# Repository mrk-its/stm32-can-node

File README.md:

# STM32 CAN Node

# Features

* modern STM32 MCU (U3/U5 series)
* integrated step-down converter (24V -> 3.3V)
* integrated CAN transceiver
* integrated 1-wire master controller (over i2c)
* 2.54 pin headers exposing 15 GPIOs
* separate SWD connector for flashing / debugging
* separate UART connector
* small form factor (40mm x 25mm)

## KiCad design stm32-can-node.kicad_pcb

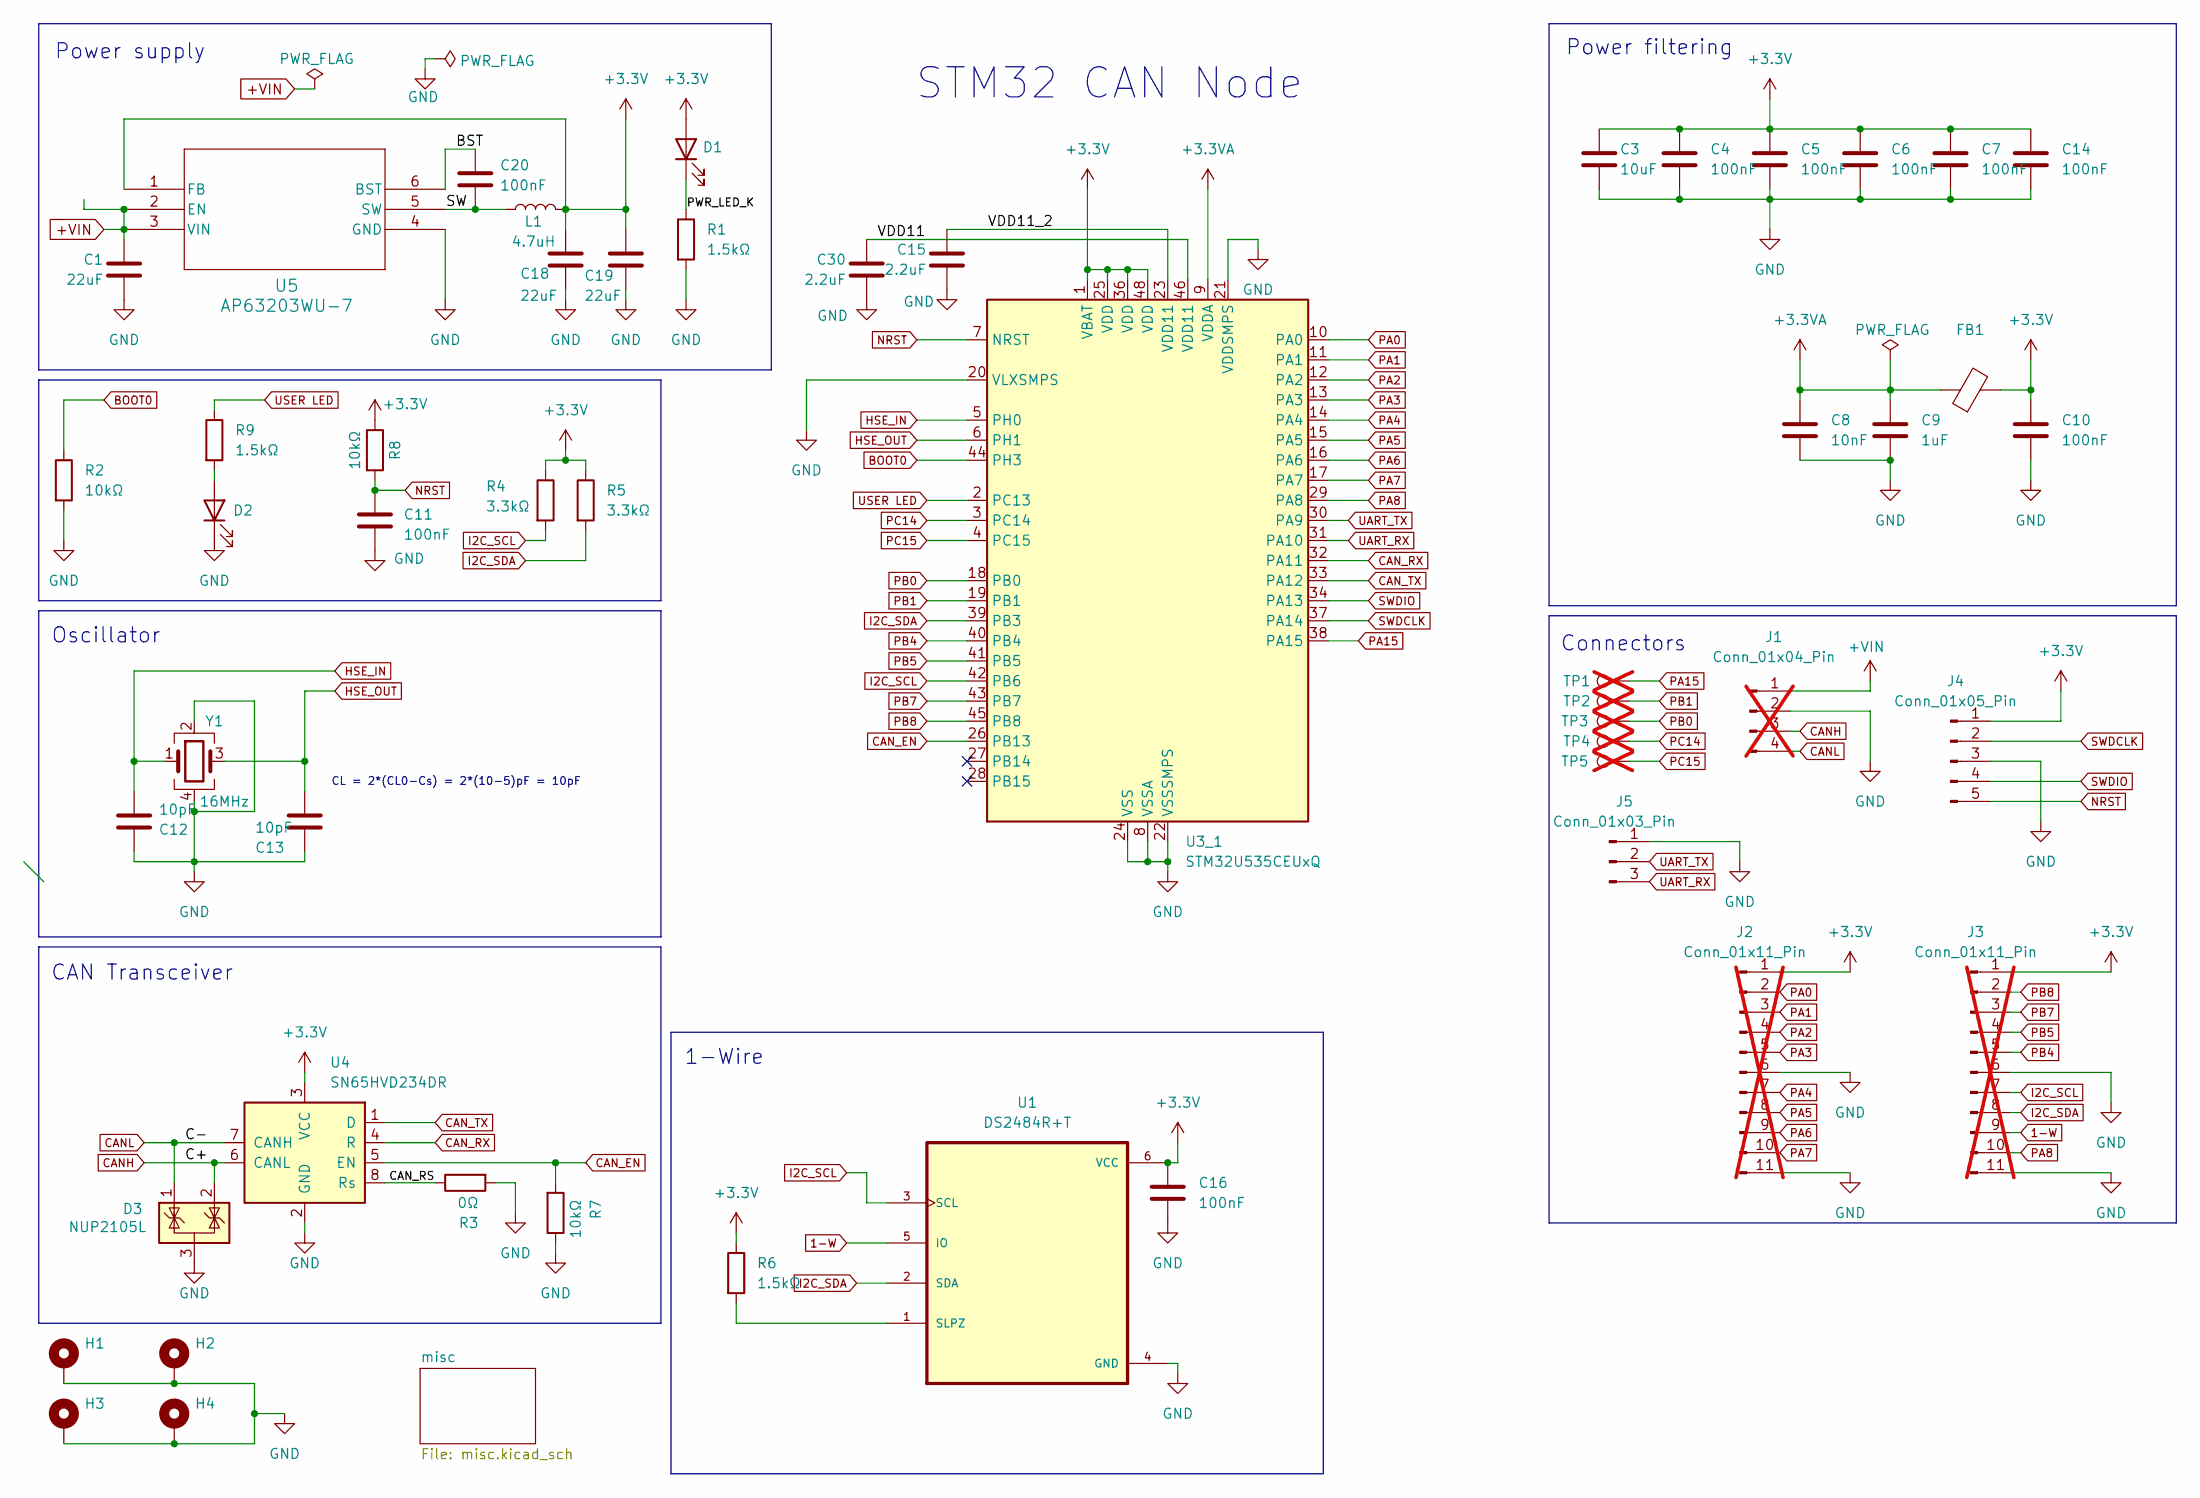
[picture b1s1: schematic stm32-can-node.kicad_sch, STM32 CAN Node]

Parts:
C1: 22uF; C_0805_2012Metric
C3: 10uF; C_0603_1608Metric
C4, C5, C6, C7, C10, C11, C14, C16, C20: 100nF; C_0402_1005Metric
C8: 10nF; C_0402_1005Metric
C9: 1uF; C_0402_1005Metric
C12, C13: 10pF; C_0402_1005Metric
C15, C30: 2.2uF; C_0603_1608Metric
C18, C19: 22uF; C_0603_1608Metric
D1: C397045; LED_0402_1005Metric
D2: C165977; LED_0402_1005Metric
D3: NUP2105L; SOT-23
FB1: FCM1608KF-601T05; L_0603_1608Metric; JLC C133937
H1, H2, H3, H4: MountingHole_Pad; MountingHole_2.2mm_M2_DIN965_Pad
J1: Conn_01x04_Pin; PinHeader_1x04_P2.54mm_Vertical; not fitted
J2, J3: Conn_01x11_Pin; PinHeader_1x11_P2.54mm_Vertical; not fitted
J4: Conn_01x05_Pin; PinHeader_1x05_P1.27mm_Vertical; JLC C2935945
J5: Conn_01x03_Pin; PinHeader_1x03_P1.27mm_Vertical; JLC C2935943
L1: 4.7uH; IND_SRP4020TA-4R7M
R1, R6, R9: 1.5kΩ; R_0402_1005Metric
R2, R7, R8: 10kΩ; R_0402_1005Metric
R3: 0Ω; R_0402_1005Metric
R4, R5: 3.3kΩ; R_0402_1005Metric
TP1, TP2, TP3, TP4, TP5: TestPoint; mini_test_point; not fitted
U1: DS2484R+T; DS2484; JLC C124886
U3_1: STM32U535CEUxQ; QFN-48-1EP_7x7mm_P0.5mm_EP5.6x5.6mm; JLC C22453481
U4: SN65HVD234DR; SOIC-8_3.9x4.9mm_P1.27mm; JLC C99818
U5: AP63203WU-7; AP63203WU-7_DIO; JLC C780769
Y1: 16MHz; Crystal_SMD_3225-4Pin_3.2x2.5mm; JLC C13738

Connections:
1-W: J3.9, U1.5 (IO)
+3.3V: C3.1, C4.1, C5.1, C6.1, C7.1, C10.1, C14.1, C16.1, C18.1, C19.1, D1.2 (A), FB1.2, J2.1, J3.1, J4.1, L1.2, R4.1, R5.1, R6.1, R8.1, U1.6 (VCC), U3_1.1 (VBAT), U3_1.25 (VDD), U3_1.36 (VDD), U3_1.48 (VDD), U4.3 (VCC), U5.1 (FB)
+3.3VA: C8.1, C9.1, FB1.1, U3_1.9 (VDDA)
+VIN: C1.1, J1.1, U5.2 (EN), U5.3 (VIN)
/BST: C20.1, U5.6 (BST)
/CAN_RS: R3.1, U4.8 (Rs)
/PWR_LED_K: D1.1 (K), R1.1
/SW: C20.2, L1.1, U5.5 (SW)
/VDD11: C30.1, U3_1.46 (VDD11)
/VDD11_2: C15.1, U3_1.23 (VDD11)
BOOT0: R2.1, U3_1.44 (PH3)
CANH: D3.2 (K), J1.3, U4.6 (CANL)
CANL: D3.1 (K), J1.4, U4.7 (CANH)
CAN_EN: R7.2, U3_1.26 (PB13), U4.5 (EN)
CAN_RX: U3_1.32 (PA11), U4.4 (R)
CAN_TX: U3_1.33 (PA12), U4.1 (D)
GND: C1.2, C3.2, C4.2, C5.2, C6.2, C7.2, C8.2, C9.2, C10.2, C11.1, C12.2, C13.2, C14.2, C15.2, C16.2, C18.2, C19.2, C30.2, D2.1 (K), D3.3 (A), H1.1, H2.1, H3.1, H4.1, J1.2, J2.6, J2.11, J3.6, J3.11, J4.3, J5.1, R1.2, R2.2, R3.2, R7.1, U1.4 (GND), U3_1.8 (VSSA), U3_1.20 (VLXSMPS), U3_1.21 (VDDSMPS), U3_1.22 (VSSSMPS), U3_1.24 (VSS), U3_1.35 (VSS), U3_1.47 (VSS), U3_1.49 (VSS), U4.2 (GND), U5.4 (GND), Y1.2, Y1.4
HSE_IN: C12.1, U3_1.5 (PH0), Y1.1
HSE_OUT: C13.1, U3_1.6 (PH1), Y1.3
I2C_SCL: J3.7, R4.2, U1.3 (SCL), U3_1.42 (PB6)
I2C_SDA: J3.8, R5.2, U1.2 (SDA), U3_1.39 (PB3)
NRST: C11.2, J4.5, R8.2, U3_1.7 (NRST)
unnamed: D2.2 (A), R9.2
unnamed: R6.2, U1.1 (SLPZ)
PA0: J2.2, U3_1.10 (PA0)
PA1: J2.3, U3_1.11 (PA1)
PA2: J2.4, U3_1.12 (PA2)
PA3: J2.5, U3_1.13 (PA3)
PA4: J2.7, U3_1.14 (PA4)
PA5: J2.8, U3_1.15 (PA5)
PA6: J2.9, U3_1.16 (PA6)
PA7: J2.10, U3_1.17 (PA7)
PA8: J3.10, U3_1.29 (PA8)
PA15: TP1.1, U3_1.38 (PA15)
PB0: TP3.1, U3_1.18 (PB0)
PB1: TP2.1, U3_1.19 (PB1)
PB4: J3.5, U3_1.40 (PB4)
PB5: J3.4, U3_1.41 (PB5)
PB7: J3.3, U3_1.43 (PB7)
PB8: J3.2, U3_1.45 (PB8)
PC14: TP4.1, U3_1.3 (PC14)
PC15: TP5.1, U3_1.4 (PC15)
SWDCLK: J4.2, U3_1.37 (PA14)
SWDIO: J4.4, U3_1.34 (PA13)
UART_RX: J5.3, U3_1.31 (PA10)
UART_TX: J5.2, U3_1.30 (PA9)
USER LED: R9.1, U3_1.2 (PC13)

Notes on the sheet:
CL = 2*(CL0-Cs) = 2*(10-5)pF = 10pF
STM32 CAN Node
Oscillator
Power filtering
1-Wire
Connectors
Power supply
CAN Transceiver

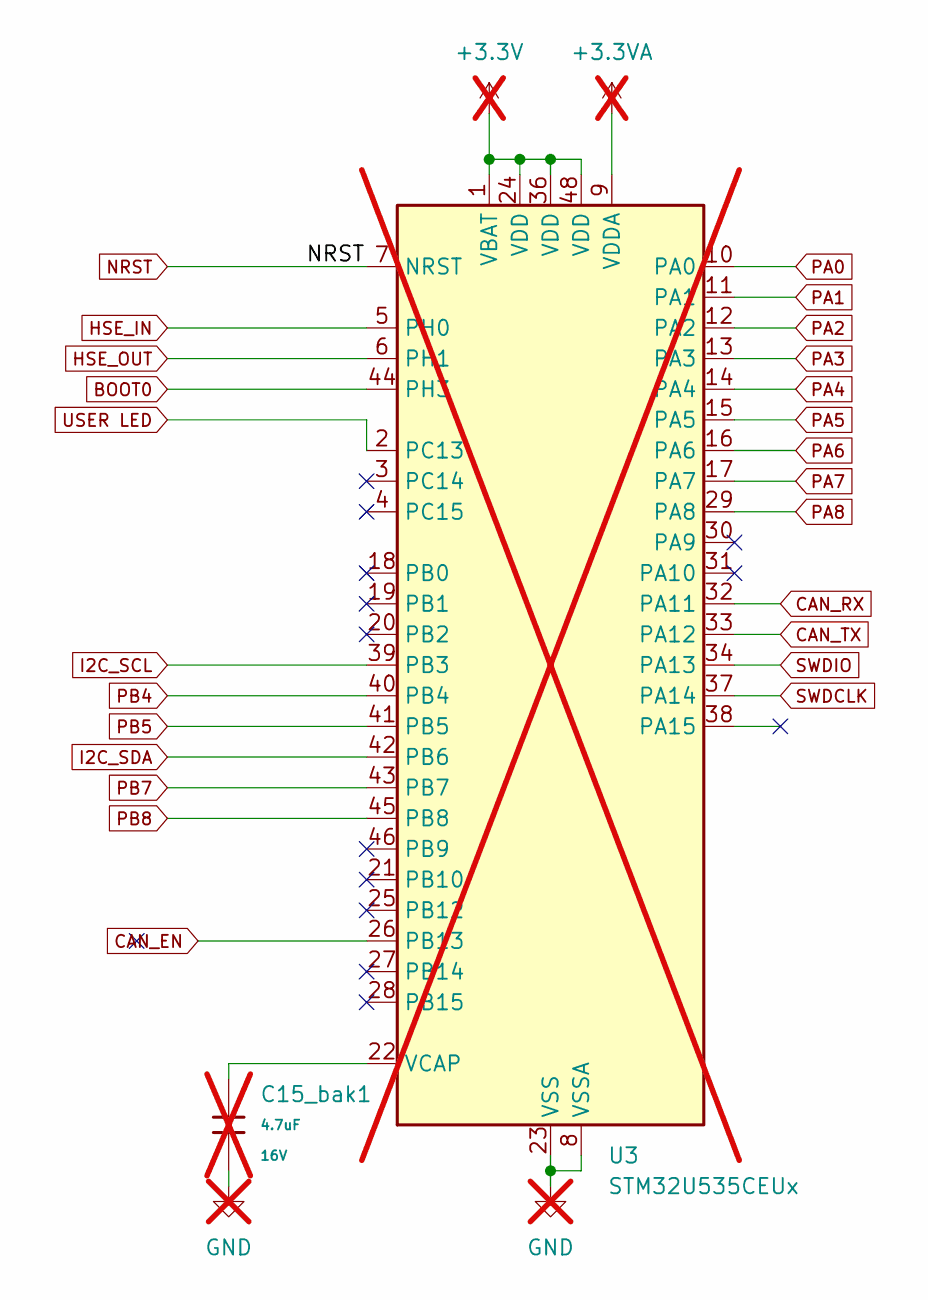
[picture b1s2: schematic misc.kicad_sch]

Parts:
C15_bak1: 4.7uF; C_0603_1608Metric; Voltage Rated 16V; Tolerance ±10%; Part CL10A475KO8NNNC; LCSC C19666; not fitted
U3: STM32U535CEUx; QFN-48-1EP_7x7mm_P0.5mm_EP5.6x5.6mm; not fitted

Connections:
unnamed: C15_bak1.1, U3.22 (VCAP)
unnamed: C15_bak1.2, U3.8 (VSSA), U3.23 (VSS), U3.35 (VSS), U3.47 (VSS), U3.49 (VSS)
unnamed: U3.1 (VBAT), U3.24 (VDD), U3.36 (VDD), U3.48 (VDD)

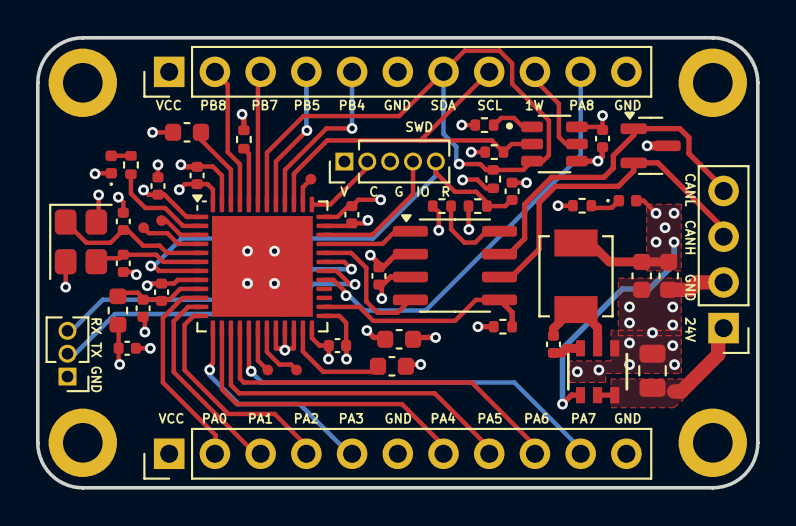
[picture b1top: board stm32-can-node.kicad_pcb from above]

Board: 4 copper layers, 40.0 x 25.0 mm, 52 parts (0 on the bottom side), 47 nets.

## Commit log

2025-05-15 initial
2025-05-15 add README.md
2025-05-16 better pcb layout
2025-05-16 update images
2025-05-16 change to 11-pin connectors
2025-05-17 add step-down converter, update part values
2025-05-17 remove vias under mcu
2025-05-19 support for UFQFPN48_SMPS
2025-05-19 add 3d models
2025-05-20 added uart header
2025-05-20 final changes before production
2025-05-21 add missing file
